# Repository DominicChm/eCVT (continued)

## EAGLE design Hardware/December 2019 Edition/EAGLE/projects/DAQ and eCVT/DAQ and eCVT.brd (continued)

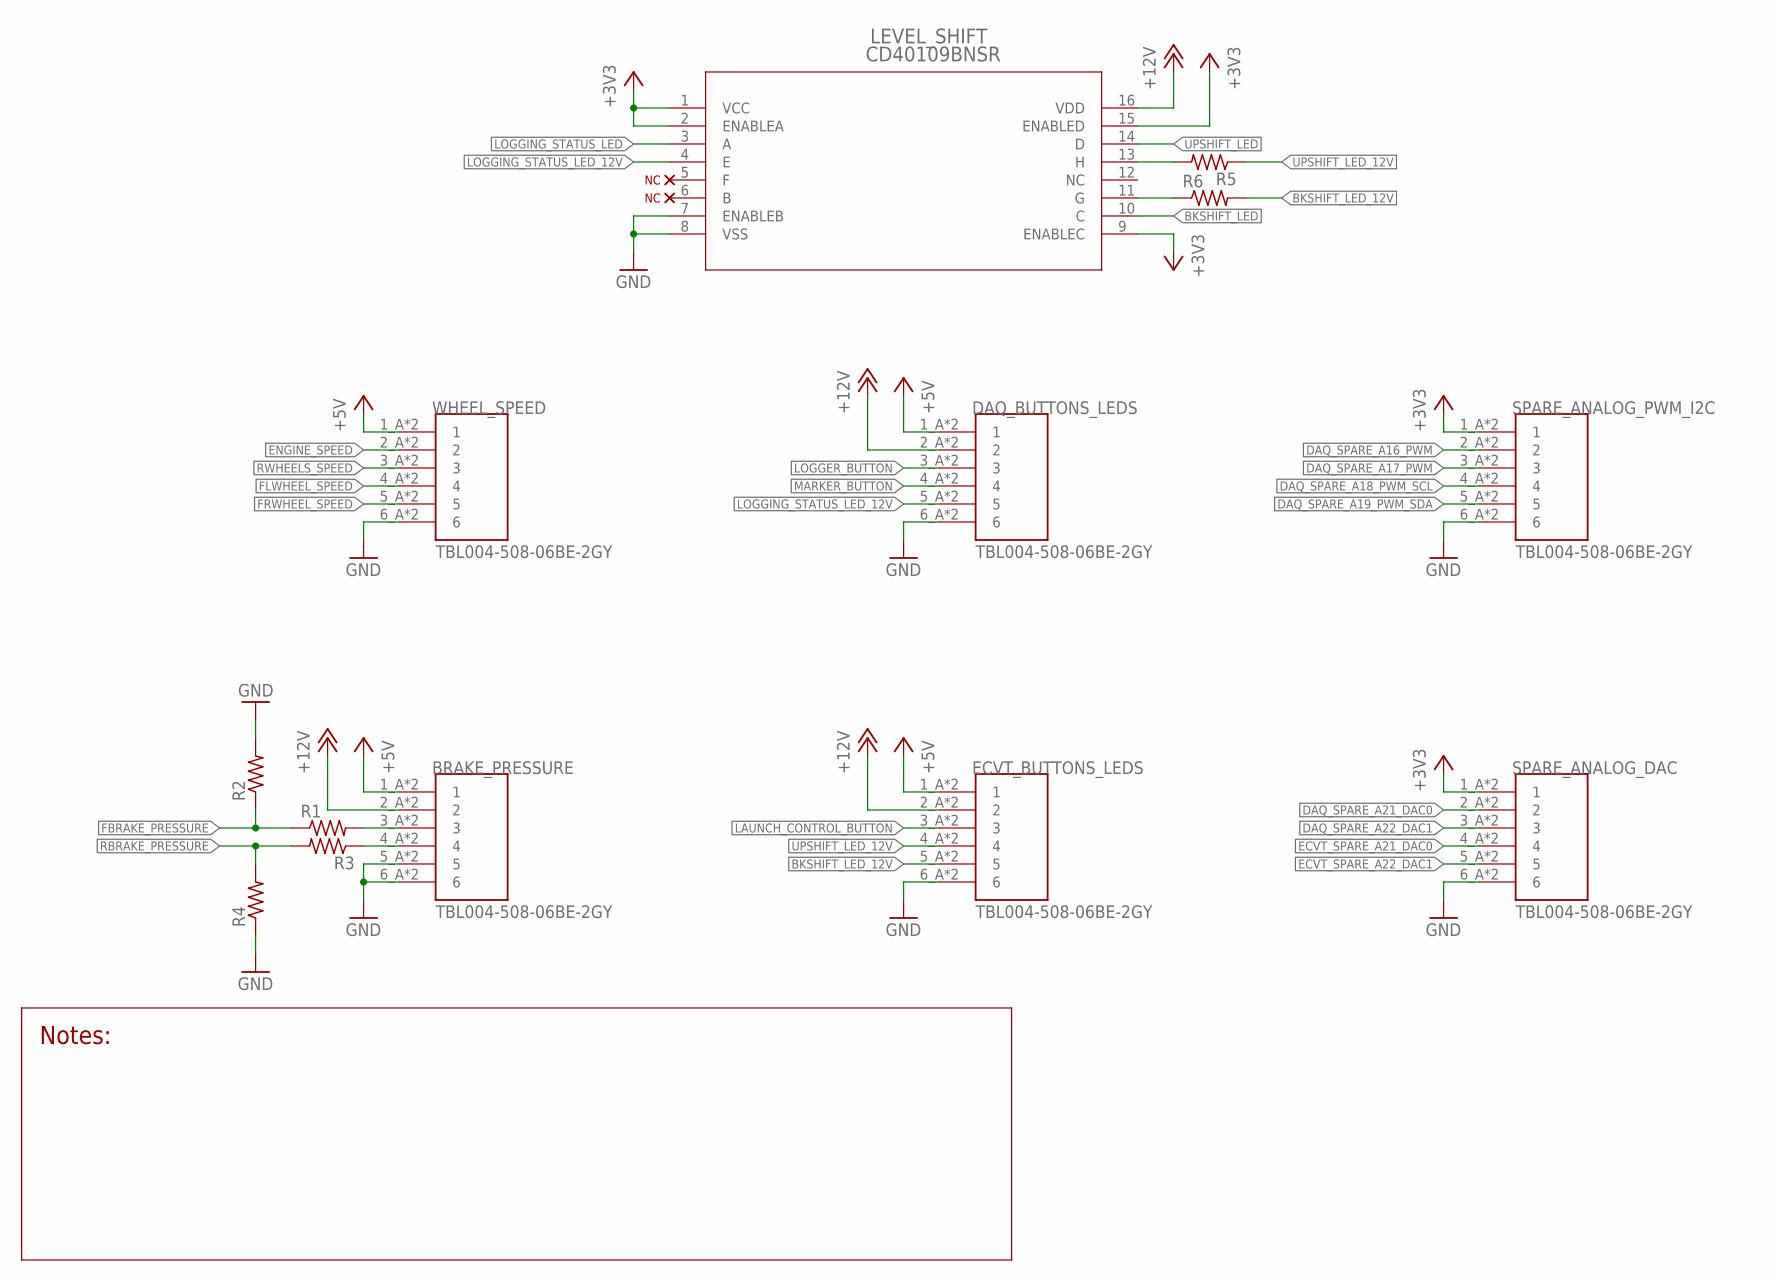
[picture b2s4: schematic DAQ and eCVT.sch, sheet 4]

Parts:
BRAKE_PRESSURE: TBL004-508-06BE-2GY; CUI_TBL004-508-06BE-2GY
DAQ_BUTTONS_LEDS: TBL004-508-06BE-2GY; CUI_TBL004-508-06BE-2GY
ECVT_BUTTONS_LEDS: TBL004-508-06BE-2GY; CUI_TBL004-508-06BE-2GY
LEVEL_SHIFT: CD40109BNSR; NS16
R1, R2, R3, R4, R5, R6: R-US_0204/7; 0204/7
SPARE_ANALOG_DAC: TBL004-508-06BE-2GY; CUI_TBL004-508-06BE-2GY
SPARE_ANALOG_PWM_I2C: TBL004-508-06BE-2GY; CUI_TBL004-508-06BE-2GY
WHEEL_SPEED: TBL004-508-06BE-2GY; CUI_TBL004-508-06BE-2GY

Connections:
+3V3: LEVEL_SHIFT.1 (VCC), LEVEL_SHIFT.2 (ENABLEA), LEVEL_SHIFT.9 (ENABLEC), LEVEL_SHIFT.15 (ENABLED), SPARE_ANALOG_DAC.1_A (1), SPARE_ANALOG_DAC.1_B (1), SPARE_ANALOG_PWM_I2C.1_A (1), SPARE_ANALOG_PWM_I2C.1_B (1); also elsewhere on the board
+5V: BRAKE_PRESSURE.1_A (1), BRAKE_PRESSURE.1_B (1), DAQ_BUTTONS_LEDS.1_A (1), DAQ_BUTTONS_LEDS.1_B (1), ECVT_BUTTONS_LEDS.1_A (1), ECVT_BUTTONS_LEDS.1_B (1), WHEEL_SPEED.1_A (1), WHEEL_SPEED.1_B (1); also elsewhere on the board
+12V: BRAKE_PRESSURE.2_A (2), BRAKE_PRESSURE.2_B (2), DAQ_BUTTONS_LEDS.2_A (2), DAQ_BUTTONS_LEDS.2_B (2), ECVT_BUTTONS_LEDS.2_A (2), ECVT_BUTTONS_LEDS.2_B (2), LEVEL_SHIFT.16 (VDD); also elsewhere on the board
BACKSHIFT_LED_12V_W/O_RES: LEVEL_SHIFT.11 (G), R6.1
BKSHIFT_LED: LEVEL_SHIFT.10 (C); also elsewhere on the board
BKSHIFT_LED_12V: ECVT_BUTTONS_LEDS.5_A (5), ECVT_BUTTONS_LEDS.5_B (5), R6.2
DAQ_SPARE_A16_PWM: SPARE_ANALOG_PWM_I2C.2_A (2), SPARE_ANALOG_PWM_I2C.2_B (2); also elsewhere on the board
DAQ_SPARE_A17_PWM: SPARE_ANALOG_PWM_I2C.3_A (3), SPARE_ANALOG_PWM_I2C.3_B (3); also elsewhere on the board
DAQ_SPARE_A18_PWM_SCL: SPARE_ANALOG_PWM_I2C.4_A (4), SPARE_ANALOG_PWM_I2C.4_B (4); also elsewhere on the board
DAQ_SPARE_A19_PWM_SDA: SPARE_ANALOG_PWM_I2C.5_A (5), SPARE_ANALOG_PWM_I2C.5_B (5); also elsewhere on the board
DAQ_SPARE_A21_DAC0: SPARE_ANALOG_DAC.2_A (2), SPARE_ANALOG_DAC.2_B (2); also elsewhere on the board
DAQ_SPARE_A22_DAC1: SPARE_ANALOG_DAC.3_A (3), SPARE_ANALOG_DAC.3_B (3); also elsewhere on the board
ECVT_SPARE_A21_DAC0: SPARE_ANALOG_DAC.4_A (4), SPARE_ANALOG_DAC.4_B (4); also elsewhere on the board
ECVT_SPARE_A22_DAC1: SPARE_ANALOG_DAC.5_A (5), SPARE_ANALOG_DAC.5_B (5); also elsewhere on the board
ENGINE_SPEED: WHEEL_SPEED.2_A (2), WHEEL_SPEED.2_B (2); also elsewhere on the board
FBRAKE_PRESSURE: R1.1, R2.1; also elsewhere on the board
FBRAKE_PRESSURE_W/O_RES: BRAKE_PRESSURE.3_A (3), BRAKE_PRESSURE.3_B (3), R1.2
FLWHEEL_SPEED: WHEEL_SPEED.4_A (4), WHEEL_SPEED.4_B (4); also elsewhere on the board
FRWHEEL_SPEED: WHEEL_SPEED.5_A (5), WHEEL_SPEED.5_B (5); also elsewhere on the board
GND: BRAKE_PRESSURE.5_A (5), BRAKE_PRESSURE.5_B (5), BRAKE_PRESSURE.6_A (6), BRAKE_PRESSURE.6_B (6), DAQ_BUTTONS_LEDS.6_A (6), DAQ_BUTTONS_LEDS.6_B (6), ECVT_BUTTONS_LEDS.6_A (6), ECVT_BUTTONS_LEDS.6_B (6), LEVEL_SHIFT.7 (ENABLEB), LEVEL_SHIFT.8 (VSS), R2.2, R4.1, SPARE_ANALOG_DAC.6_A (6), SPARE_ANALOG_DAC.6_B (6), SPARE_ANALOG_PWM_I2C.6_A (6), SPARE_ANALOG_PWM_I2C.6_B (6), WHEEL_SPEED.6_A (6), WHEEL_SPEED.6_B (6); also elsewhere on the board
LAUNCH_CONTROL_BUTTON: ECVT_BUTTONS_LEDS.3_A (3), ECVT_BUTTONS_LEDS.3_B (3); also elsewhere on the board
LOGGER_BUTTON: DAQ_BUTTONS_LEDS.3_A (3), DAQ_BUTTONS_LEDS.3_B (3); also elsewhere on the board
LOGGING_STATUS_LED: LEVEL_SHIFT.3 (A); also elsewhere on the board
LOGGING_STATUS_LED_12V: DAQ_BUTTONS_LEDS.5_A (5), DAQ_BUTTONS_LEDS.5_B (5), LEVEL_SHIFT.4 (E)
MARKER_BUTTON: DAQ_BUTTONS_LEDS.4_A (4), DAQ_BUTTONS_LEDS.4_B (4); also elsewhere on the board
RBRAKE_PRESSURE: R3.2, R4.2; also elsewhere on the board
RBRAKE_PRESSURE_W/O_RES: BRAKE_PRESSURE.4_A (4), BRAKE_PRESSURE.4_B (4), R3.1
RWHEELS_SPEED: WHEEL_SPEED.3_A (3), WHEEL_SPEED.3_B (3); also elsewhere on the board
UPSHIFT_LED: LEVEL_SHIFT.14 (D); also elsewhere on the board
UPSHIFT_LED_12V: ECVT_BUTTONS_LEDS.4_A (4), ECVT_BUTTONS_LEDS.4_B (4), R5.1
UPSHIFT_LED_12V_W/O_RES: LEVEL_SHIFT.13 (H), R5.2

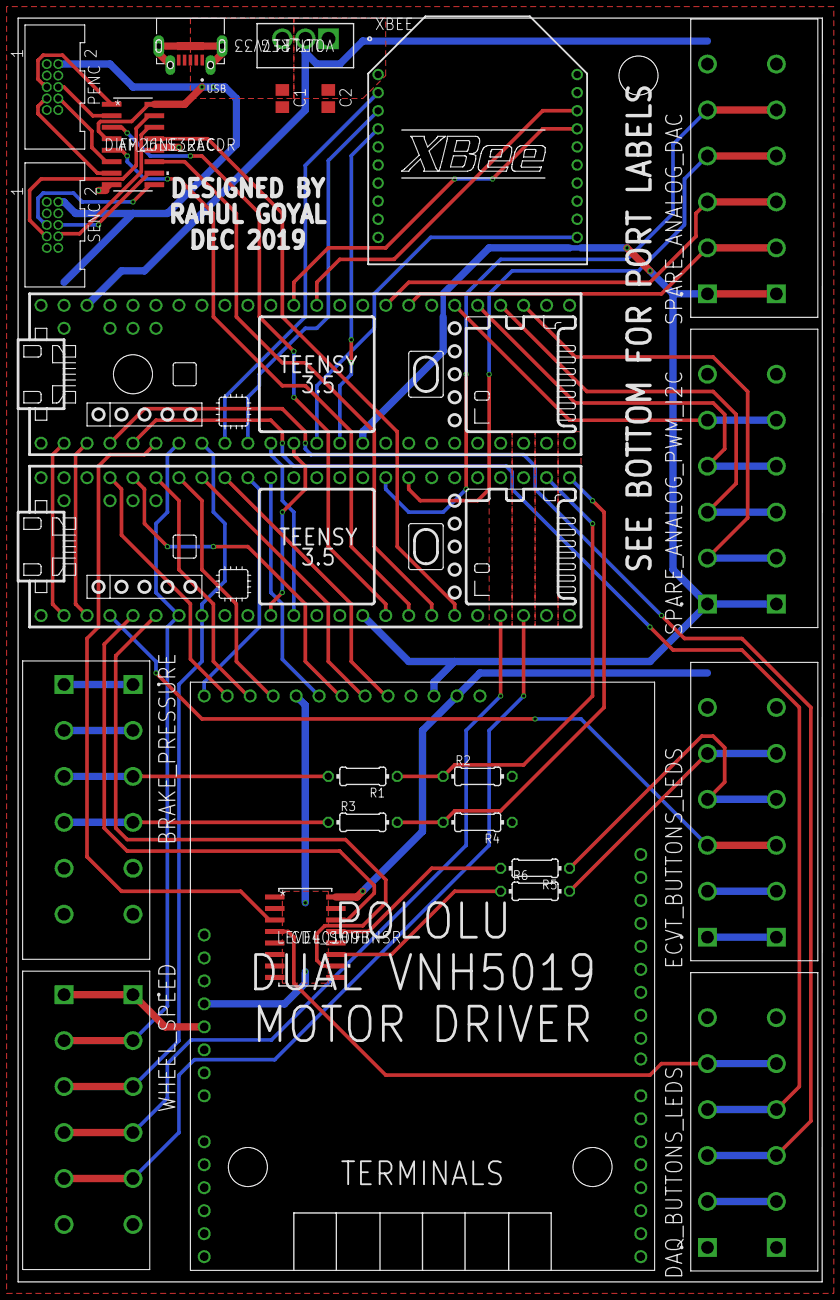
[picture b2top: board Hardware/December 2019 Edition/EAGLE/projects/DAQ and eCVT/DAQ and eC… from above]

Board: 2 copper layers, 88.9 x 139.7 mm, 24 parts (0 on the bottom side), 64 nets.

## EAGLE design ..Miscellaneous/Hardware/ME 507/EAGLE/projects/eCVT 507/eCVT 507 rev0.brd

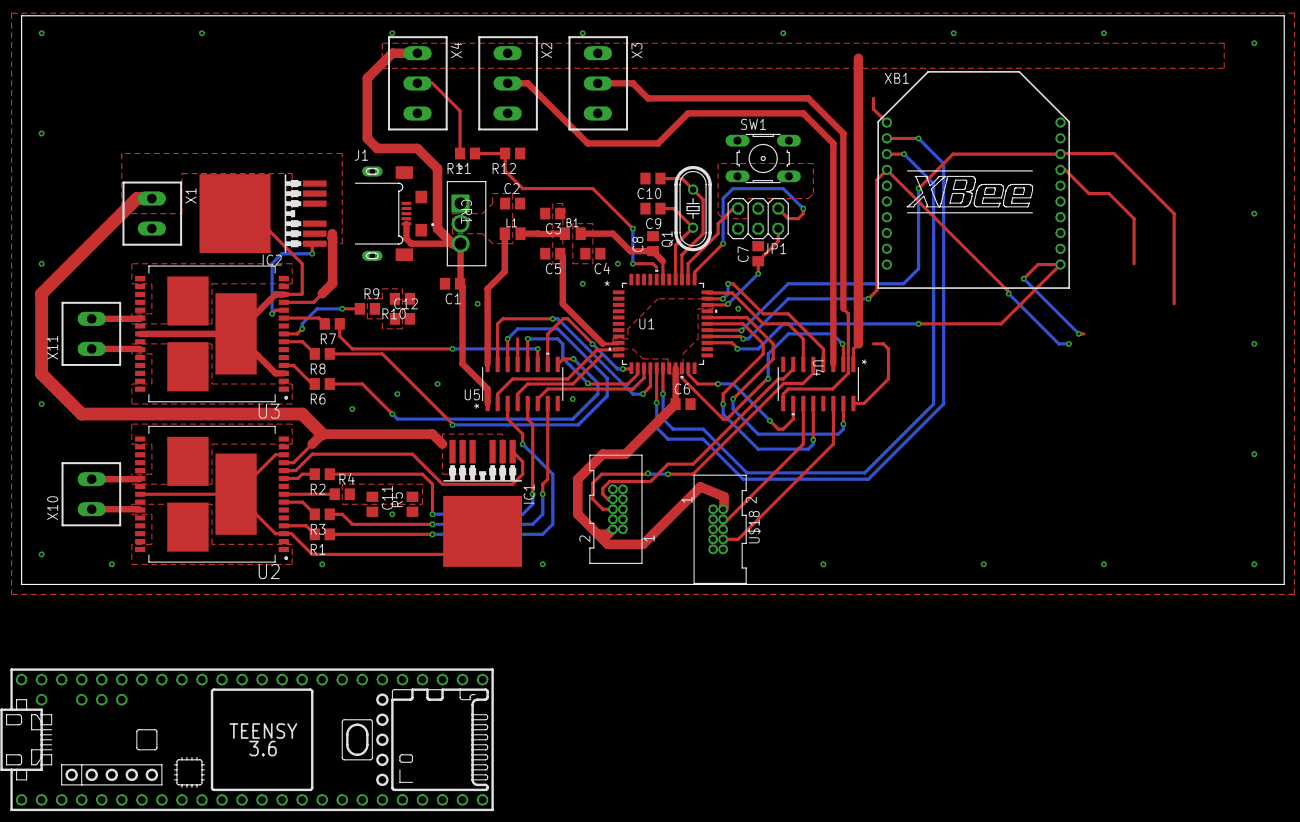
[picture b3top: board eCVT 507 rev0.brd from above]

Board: 2 copper layers, 160.0 x 72.1 mm, 48 parts (0 on the bottom side), 61 nets.

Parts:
B1: 220@100MHz; 0805
C1: 100nF; C0805
C2, C3, C4: 10uF; C0805
C5, C6, C7, C8: 0.1uF; C0805
C9, C10: 30pF; C0805
C11, C12: C0805
CR1: LD1117V33; TO-220
IC1, IC2: IPB180N06S4-H1; PG-TO263-7-3
J1: UJ2-MIBH-4-MSMT; CUI_UJ2-MIBH-4-MSMT
JP1: 2X03
L1: 10uH; 0805
Q1: 16MHz 18pF; HC49/S
R1, R2, R3, R6, R7, R8: 1K; R0805
R4, R9: 10K; R0805
R5, R10: 1.5K; R0805
R11: 1.7K; R0805
R12: 3.3K; R0805
SW1: SW; B3F-10XX
U1: ATXMEGA128A4U-AU; 44A
U2, U3: VNH5019ATR-E; IC_VNH5019ATR-E
U4, U5: MC14504BDR2G; SOIC-16
U$3: TEENSY_3.5/3.6_BASIC
U$18, U$19: SHF-105-01-X-D-TH
X1, X10, X11: 2POL381
X2, X3, X4: 3POL381
XB1: XBEE

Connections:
+3V3: C2.1, CR1.2, L1.1, U4.16, U5.16, XB1.1
+5V: C1.1, CR1.3, J1.1, U4.1, U5.1, U$3.VIN, X2.1, X3.1, X4.1
+12V: IC1.2, IC1.3, IC1.5, IC1.6, IC1.7, IC2.2, IC2.3, IC2.5, IC2.6, IC2.7, U2.12, U3.12, X1.1
AVCC: B1.2, C4.1, C8.1, U1.39
BRAKE_PRESSURE: R11.1, R12.2
ENGINE_SPEED: U4.3, X2.2
ENGINE_SPEED_3V3: U1.40, U4.2
GND: C1.2, C2.2, C3.2, C4.2, C5.2, C6.2, C7.2, C8.2, C9.2, C10.2, C11.2, C12.2, CR1.1, J1.5, JP1.6, R5.1, R10.1, R12.1, SW1.1, SW1.2, U1.8, U1.18, U1.30, U1.38, U2.18, U2.19, U2.20, U2.26, U2.27, U2.28, U3.18, U3.19, U3.20, U3.26, U3.27, U3.28, U4.8, U5.8, U$3.AGND, U$3.GND, U$3.GND2, U$18.3, U$19.3, X1.2, X2.3, X3.3, X4.3, XB1.10
MISO: U1.26, U$3.12/MISO, XB1.4
MOSI: U1.25, U$3.11/MOSI, XB1.11
unnamed: R1.2, U2.4
unnamed: R2.2, U2.10
unnamed: R4.1, U2.8
unnamed: C11.1, R4.2, R5.2
unnamed: U2.15, U2.16, U2.21, U2.HS3, X10.2
unnamed: U2.1, U2.25, U2.30, U2.HS2, X10.1
unnamed: IC1.1, U2.11
unnamed: R3.2, U2.7
unnamed: IC1.8, U2.3, U2.13, U2.23, U2.HS1
unnamed: R6.2, U3.4
unnamed: R7.2, U3.10
unnamed: R8.2, U3.7
unnamed: R9.1, U3.8
unnamed: C12.1, R9.2, R10.2
unnamed: U3.15, U3.16, U3.21, U3.HS3, X11.2
unnamed: U3.1, U3.25, U3.30, U3.HS2, X11.1
unnamed: IC2.1, U3.11
unnamed: IC2.8, U3.3, U3.13, U3.23, U3.HS1
unnamed: R11.2, X4.2
PDI_DATA: JP1.1, U1.34
PENC_INA: U4.11, U$18.6
PENC_INA_3V3: U1.28, U4.12
PENC_INB: U4.14, U$18.8
PENC_INB_3V3: U1.29, U4.15
PMOT_INA: R1.1, U5.3
PMOT_INA_3V3: U1.4, U5.2
PMOT_INB: R2.1, U5.5
PMOT_INB_3V3: U1.5, U1.7, U5.4
PMOT_PWM: R3.1, U5.7
PMOT_PWM_3V3: U1.14, U5.6
RESET/PDI_CLK: JP1.5, SW1.3, SW1.4, U1.35
RWHEEL_SPEED: U4.9, X3.2
RWHEEL_SPEED_3V3: U1.41, U4.10
SCK: U1.27, U$3.13/SCK, XB1.18
SENC_INA: U4.5, U$19.6
SENC_INA_3V3: U1.32, U4.4
SENC_INB: U4.7, U$19.8
SENC_INB_3V3: U1.33, U4.6
SMOT_INA: R6.1, U5.9
SMOT_INA_3V3: U1.6, U5.10
SMOT_INB: R7.1, U5.11
SMOT_PWM: R8.1, U5.14
SMOT_PWM_3V3: U1.15, U5.15
SS: U$3.10/CS, XB1.17
TEENSY_RX: U1.12, U$3.8
TEENSY_TX: U1.13, U$3.7
VCC: B1.1, C3.1, C5.1, C6.1, C7.1, JP1.2, L1.2, U1.9, U1.19, U1.31, U$18.2, U$19.2
XBEE_RX: U1.16, XB1.2
XBEE_TX: U1.17, XB1.3
XTAL1: C9.1, Q1.1, U1.37
XTAL2: C10.1, Q1.2, U1.36

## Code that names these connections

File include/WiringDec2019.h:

/*
 *  WiringDec2019.h - DAQ and eCVT wiring configuration.
 *  Created by Rahul Goyal, December 2019.
 *  Released to Cal Poly Baja SAE. ;)
 */

#ifndef WiringDec2019_h
#define WiringDec2019_h

#include <Arduino.h>

// Hall Effect Sensors
const int8_t  ENGINE_SPEED_PIN =  5;
const int8_t RWHEELS_SPEED_PIN =  6;
const int8_t FLWHEEL_SPEED_PIN = 29;
const int8_t FRWHEEL_SPEED_PIN = 30;

// Encoders
/* Swap A and B pins to swap direction. */
const int8_t P_ENC_A = 24;
const int8_t P_ENC_B = 25;
const int8_t S_ENC_A = 27;
const int8_t S_ENC_B = 26;

// Motors
/* Swap A and B pins to swap direction. */
const int8_t P_MOT_INA = 19;
const int8_t P_MOT_INB = 18;
const int8_t P_MOT_PWM = 22;
const int8_t S_MOT_INA = 20;
const int8_t S_MOT_INB = 21;
const int8_t S_MOT_PWM = 23;

// Pressure Transducers
const int8_t FBRAKE_PRESSURE = 34;
const int8_t RBRAKE_PRESSURE = 33;

// Dashboard
const int8_t LOGGER_BUTTON = 2;
const int8_t MARKER_BUTTON = 3;
const int8_t LAUNCH_BUTTON = 2;
const int8_t  DAQ_STATUS_LED = 4;
const int8_t ECVT_STATUS_LED = 0;
const int8_t UPSHIFT_LED = 3;
const int8_t BKSHIFT_LED = 4;

// Communication
#define DAQ_ECVT_SERIAL Serial1
#define DAQ_XBEE_SERIAL Serial2

#endif

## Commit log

2019-06-02 Initial simulation (needs work)
2019-06-02 It kind of works
2019-06-02 Added scope block
2019-06-02 Improved (fixed) stability by changing divide order
2019-06-02 Commented blocks
2019-06-02 Added complex loop + commenting
2019-06-03 Simple simulation works reasonably
2019-06-03 Organized files
2019-06-03 Made PID and bang bang with actuator
2019-06-03 Added PID pictures and lookup table
2019-07-01 PDR figures, etc.
2019-10-30 CDR Progress
2019-11-04 Uploaded board design for 507
2019-11-04 Added level shifters, xbee, other fixes
2019-11-07 Updated wiring schematic
2019-12-08 Started December 2019 board
2019-12-08 Reorganization
2019-12-08 Progress
2019-12-09 Update eCVT 507 and reorganize
2019-12-09 Finished schematic? (except LED wiring)
2019-12-09 Finished schematic!
2019-12-10 Started board
2019-12-12 Finished board layout, need to add mounting holes and writing
2019-12-12 December 2019 board finished
2019-12-19 Update EngineSpeed library
2019-12-21 Commented libraries
2019-12-21 Created EngineSpeed testing configuration
2019-12-21 Updated pins and lookup table
2020-01-15 Ditch unsigned integers where unnecessary, updates from Monday bench testing
2020-01-17 Friday bench testing with engine runnning no belt
2020-01-19 Some untested formatting changes
2020-01-19 More untested formatting changes
2020-01-19 Minor formatting update
2020-01-21 Fix keywords.txt files
2020-01-21 Untested code organization, documentation, new FSMs setup, interrupt protection
2020-01-21 Move debugging statements for consistent serial monitor printout
2020-01-21 Untested additional pin configurations and commenting
2020-01-21 Untested launch control and dashboard LEDs functionality
2020-01-25 Untested changes (improved formatting, removed floats, more)
2020-02-03 First implementation of DAQ code (slow, ~50Hz, will improve drastically)
2020-02-03 Untested changes (improved formatting, began communication code)
2020-02-03 Untested changes (changed dashboard states)
2020-02-21 Rewired Teensys for February edition, pending full rewire
2020-02-21 Removed extraneous files
2020-02-21 Fixed the spelling of February
2020-02-21 Finished schematic except RJ45 connectors and LEDs, need to redo board
2020-02-22 Finished schematic, need to check LED wiring
2020-02-22 Rename old board file
2020-02-25 Wiring the board...
2020-02-27 Untested new lookup table, communication setup
2020-02-28 Thursday bench testing with engine running and belt
2020-03-02 Untested config generalization, calibration ready, hall effect sensor task, launch button fix
2020-03-02 Untested DAQ overhaul
2020-03-02 It is now March
2020-03-03 Change start byte to 0x8080
2020-03-03 Untested add get individual P, I, D to PIDController class
2020-03-06 Untested calibration changes
2020-03-06 Thursday bench testing with improved secondary calibration, need to improve primary calibration
2020-03-06 Untested max static duty cycle protection implementation
2020-03-09 Checkpoint before rewiring spring terminals to front/back instead of wheelspeed/brakepressure
2020-03-09 Almost done wiring the board!
2020-03-09 No DRC errors! Need to do a final check + board writing
2020-03-10 Small board revisions before sending out
2020-03-10 Ready to send out
2020-03-29 Restore motor library reference
2020-03-29 File organization
2020-07-26 Minor formatting changes
2020-08-10 Migrate to Platform IO
2020-08-10 Organize miscellaneous folder
2020-08-10 Revert "Organize miscellaneous folder"
    This reverts commit b2e9b54aeb2ddac7953c990eb7f5dec07fb12651.
2020-08-10 Move files into correct folders (include, libraries, main)
2020-08-24 Rename miscellaneous folder
2020-08-30 Start interrupts after rear wheel speed read
2020-08-30 Get ratio from ePID instead of pPID
2020-08-30 Fix secondary static duty cycle condition
2020-10-17 Add clutch control overview (for pdr)
2020-12-23 Create temporary function declarations so code compiles
2020-12-23 Uncomment communication fsm
2020-12-23 Update library headers
2020-12-23 Remove obnoxious extra spacing between fsm functions
2020-12-30 Create FSMVariables class
2020-12-30 Create Task class
2020-12-30 Create ControlLoop class
2020-12-30 Create Clutch class
2020-12-30 Create Primary and Secondary classes
2020-12-30 Create Engine class
2020-12-30 Put LookupTables in separate header file
2020-12-30 Move Clutch to src
2020-12-30 Create Communication class
2020-12-31 Create LaunchControl class
2021-01-07 Create DashboardLED class
2021-01-07 Remove need to include wiring info in LaunchControl
2021-01-07 Create Sensor class
2021-01-14 Update EngineSpeed and WheelSpeed
2021-01-14 Create HallEffectTask class
2021-01-14 Refactor main
2021-01-17 Remove FSMVars from sensors
2021-01-17 Add newline at end of file
2021-01-18 Add newline to LookupTables
2021-01-21 Fix comment spacing in Clutch.cpp
2021-01-21 Add back updated main header
2021-01-21 Credit Shaina for library abstractions
2021-01-21 Fix indent and move FSMVars to src
2021-01-28 Move FSMVars and Task, rename DashboardLED
2021-01-28 Move timers to main
2021-01-31 Add virutal getState to ControlLoop
2021-02-15 Fix lookup table indentation
2021-02-15 Update file header spacing
2021-02-18 Improve Clutch formatting
2021-02-18 Improve Communication formatting
2021-02-18 Improve ControlLoop formatting
2021-02-18 Improve DashboardLEDs formatting
2021-02-18 Improve Engine formatting
2021-02-18 Improve HallEffectTask formatting
2021-02-18 Improve LaunchControl formatting
2021-02-18 Improve Primary formatting
2021-02-18 Improve Secondary formatting
2021-02-18 Improve FSMVars formatting
2021-02-18 Improve main formatting
2021-02-18 Fix if statement spacing
2021-02-18 Replace main tabs with spaces
2021-04-12 Create brake pressure class
2021-04-12 Add brake pressure variables to fsm vars
2021-04-12 Update launch control fsm to use brake pressure from fsm vars
2021-04-12 Create pressure transducer task
2021-04-12 Add pressure transducer task to main
2021-09-25 Autoformat libraries
2021-09-25 Autoformat source code
2021-09-26 Remove unnecessary member variables
2021-09-26 Simplify PID controller code
2022-01-12 Add HX711 library
2022-01-12 Create load cell library
    Wrap HX711 library for now
2022-01-13 Move controller from clutch to primary/secondary
2022-01-13 Add load cell control loop to secondary
2022-01-14 Move ratio to setpoint conversion from engine to primary/secondary
2022-01-14 Add load cell to communication
2022-01-15 Fix load cell calibration factor
2022-01-15 Add documentation and initial tune
2022-01-15 Update engine speed triggers
2022-01-15 Fix brake pressure read
2022-01-15 Initialize state vars
2022-01-16 Add WiringDec2021.h
2022-01-16 Use new wiring in code
    Ignore brake pressure for now
2022-01-16 Check load cell force when setting motor duty cycle
    Set motor duty cycle to 0 if load cell force too high
2022-01-16 Change load cell calibration factor from float to 32-bit int
    Ben changed the parameter but not the member variable
2022-01-16 Change load cell value from 32-bit int to 16-bit int
    It should not be a 32-bit int with the calibration factor changes, and the read() method returns a 16-bit int anyway
2022-01-17 Read magnitude of load cell force
2022-01-17 Create load cell task
2022-01-17 Use load cell task
2022-01-17 Protect public abstract methods
2022-01-17 Shorten method name
2022-01-17 Refactor safe set motor duty cycle logic
2022-01-17 Increase safe check efficiency
    The safe check is called often. Do floating-point arithmetic once on setup, then only do integer comparisons.
2022-01-17 Add load cell pins and calibration
2022-01-17 Move FSM variables initialization from main to header
2022-01-17 Move interrupt service routines to remove function prototypes
2022-01-17 Add motor/encoder direction test script
2022-01-20 Update lookup tables
2022-01-20 Add load cell testing to TEST in main
2022-01-29 Communication changes
2022-02-03 Pass FSMVars by reference
2022-02-06 Fix motor and encoder directions
2022-02-06 Disable test mode
2022-02-06 Change comment spacing
2022-02-07 Fix hall effect sensor interrupt service routines
2022-02-07 Pass encoder by reference
2022-02-10 Reorder parameters
2022-02-10 Enable clamping force lookup table
2022-02-10 Replace unnecessary "else if" with "if" statements
2022-02-11 Use load cell to detect calibration zero
    Reorder constants
2022-02-11 Remove verbose clamping function brackets
2022-02-11 Use 16-bit integer for PID saturations
2022-02-11 Read load cell force vector not force magnitude
2022-02-11 Clamp PID output
2022-02-15 gigore
2022-02-17 Fix communications lib
